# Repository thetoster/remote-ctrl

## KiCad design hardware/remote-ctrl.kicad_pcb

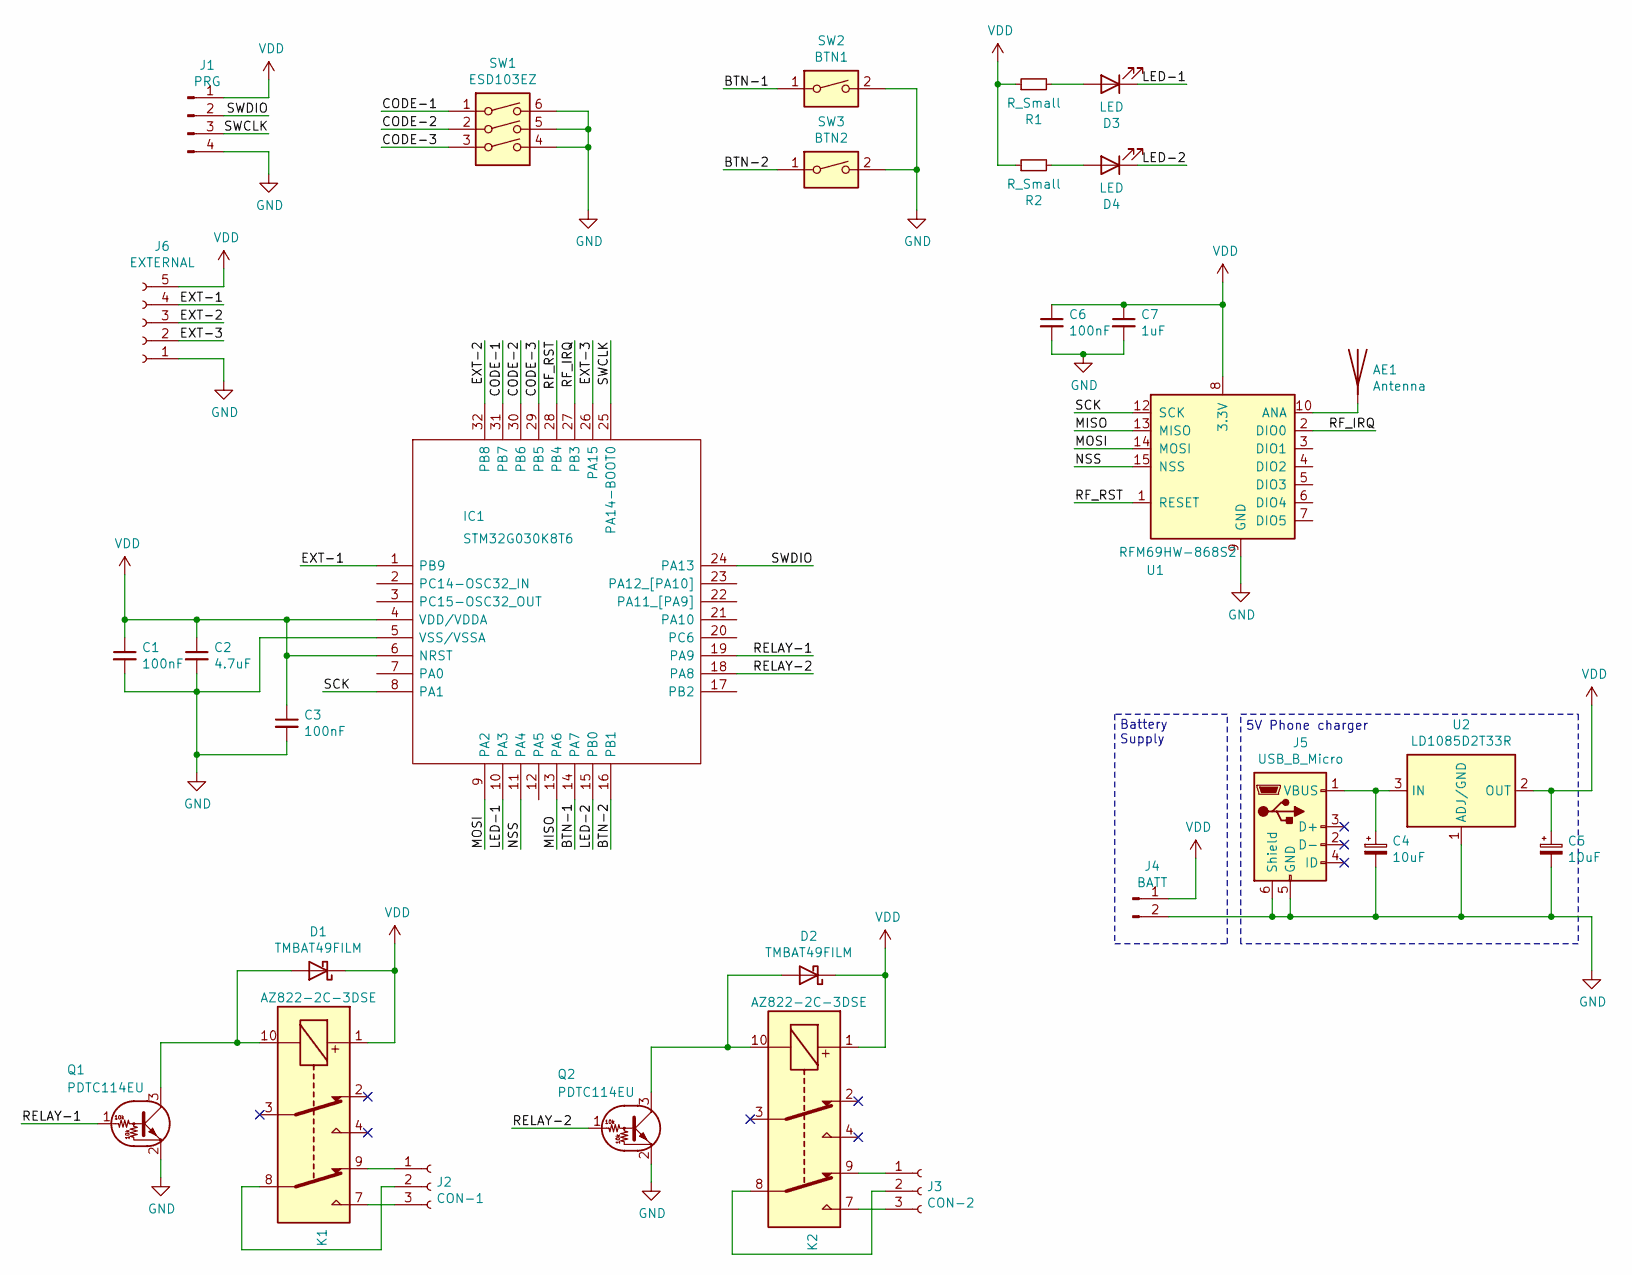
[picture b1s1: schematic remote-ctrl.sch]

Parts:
AE1: Antenna; TestPoint_Pad_2.0x2.0mm
C1, C3, C6: 100nF; C_0805_2012Metric_Pad1.15x1.40mm_HandSolder
C2: 4.7uF; C_0805_2012Metric_Pad1.15x1.40mm_HandSolder
C4, C5: 10uF; CP_Elec_4x5.3
C7: 1uF; C_0805_2012Metric_Pad1.15x1.40mm_HandSolder
D1, D2: TMBAT49FILM; D_MELF
D3, D4: LED; D_1206_3216Metric
IC1: STM32G030K8T6; QFP80P900X900X160-32N; Manufacturer_Part_Number STM32G030K8T6; Mouser Part Number 511-STM32G030K8T6
J1: PRG; PinHeader_1x04_P2.54mm_Vertical
J2: CON-1; TerminalBlock_bornier-3_P5.08mm
J3: CON-2; TerminalBlock_bornier-3_P5.08mm
J4: BATT; PinHeader_1x02_P2.54mm_Vertical
J5: USB_B_Micro; USB_Micro-B_Molex-105017-0001
J6: EXTERNAL; PinHeader_1x05_P2.54mm_Vertical
K1, K2: AZ822-2C-3DSE; Relay_DPDT_FRT5
Q1, Q2: PDTC114EU; SOT-323_SC-70_Handsoldering
R1, R2: R_Small; R_0805_2012Metric_Pad1.15x1.40mm_HandSolder
SW1: ESD103EZ; SW_DIP_SPSTx03_Slide_9.78x9.8mm_W8.61mm_P2.54mm
SW2: BTN1; SW_SPST_Omron_B3FS-101xP
SW3: BTN2; SW_SPST_Omron_B3FS-101xP
U1: RFM69HW-868S2; HOPERF_RFM69HW
U2: LD1085D2T33R; TO-263-3_TabPin2

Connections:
/BTN-1: IC1.14 (PA7), SW2.1
/BTN-2: IC1.16 (PB1), SW3.1
/CODE-1: IC1.31 (PB7), SW1.1
/CODE-2: IC1.30 (PB6), SW1.2
/CODE-3: IC1.29 (PB5), SW1.3
/EXT-1: IC1.1 (PB9), J6.4
/EXT-2: IC1.32 (PB8), J6.3
/EXT-3: IC1.26 (PA15), J6.2
/LED-1: D3.1 (K), IC1.10 (PA3)
/LED-2: D4.1 (K), IC1.15 (PB0)
/MISO: IC1.13 (PA6), U1.13 (MISO)
/MOSI: IC1.9 (PA2), U1.14 (MOSI)
/NSS: IC1.11 (PA4), U1.15 (NSS)
/RELAY-1: IC1.19 (PA9), Q1.1 (B)
/RELAY-2: IC1.18 (PA8), Q2.1 (B)
/RF_IRQ: IC1.27 (PB3), U1.2 (DIO0)
/RF_RST: IC1.28 (PB4), U1.1 (RESET)
/SCK: IC1.8 (PA1), U1.12 (SCK)
/SWCLK: IC1.25 (PA14-BOOT0), J1.3
/SWDIO: IC1.24 (PA13), J1.2
GND: C1.2, C2.2, C3.2, C4.2, C5.2, C6.2, C7.2, IC1.5 (VSS/VSSA), J1.4, J4.2, J5.5 (GND), J5.6 (Shield), J6.1, Q1.2 (E), Q2.2 (E), SW1.4, SW1.5, SW1.6, SW2.2, SW3.2, U1.9 (GND), U1.11 (GND), U2.1 (ADJ/GND)
unnamed: AE1.1, U1.10 (ANA)
unnamed: C4.1, J5.1 (VBUS), U2.3 (IN)
unnamed: D1.2 (A), K1.10, Q1.3 (C)
unnamed: D2.2 (A), K2.10, Q2.3 (C)
unnamed: D3.2 (A), R1.2
unnamed: D4.2 (A), R2.2
unnamed: J2.1, K1.9
unnamed: J2.2, K1.8
unnamed: J2.3, K1.7
unnamed: J3.1, K2.9
unnamed: J3.2, K2.8
unnamed: J3.3, K2.7
VDD: C1.1, C2.1, C3.1, C5.1, C6.1, C7.1, D1.1 (K), D2.1 (K), IC1.4 (VDD/VDDA), IC1.6 (NRST), J1.1, J4.1, J6.5, K1.1, K2.1, R1.1, R2.1, U1.8 (3.3V), U2.2 (OUT)

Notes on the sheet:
Battery Supply
5V Phone charger

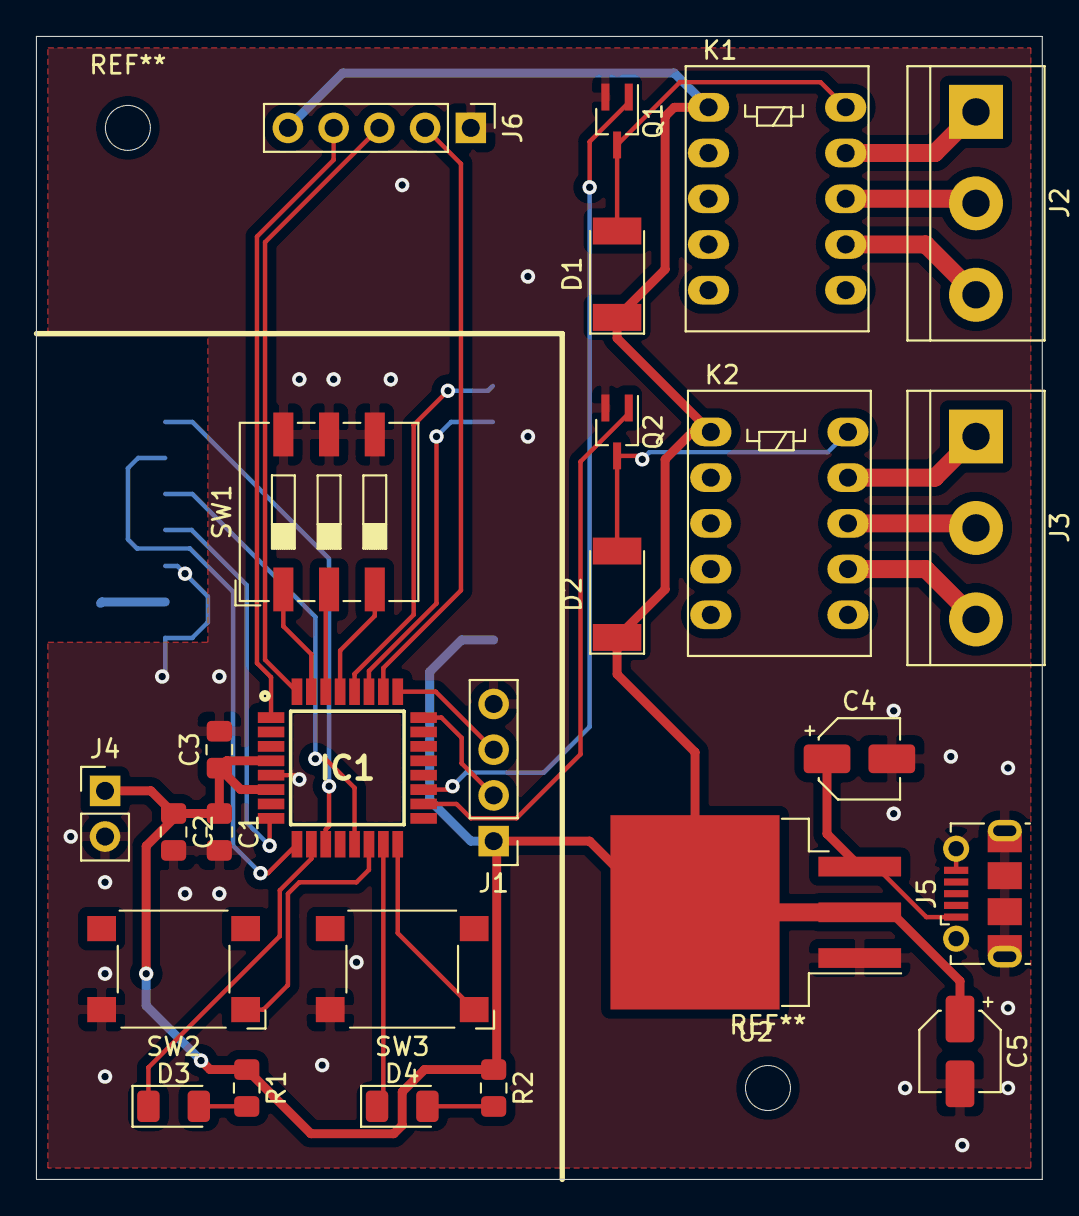
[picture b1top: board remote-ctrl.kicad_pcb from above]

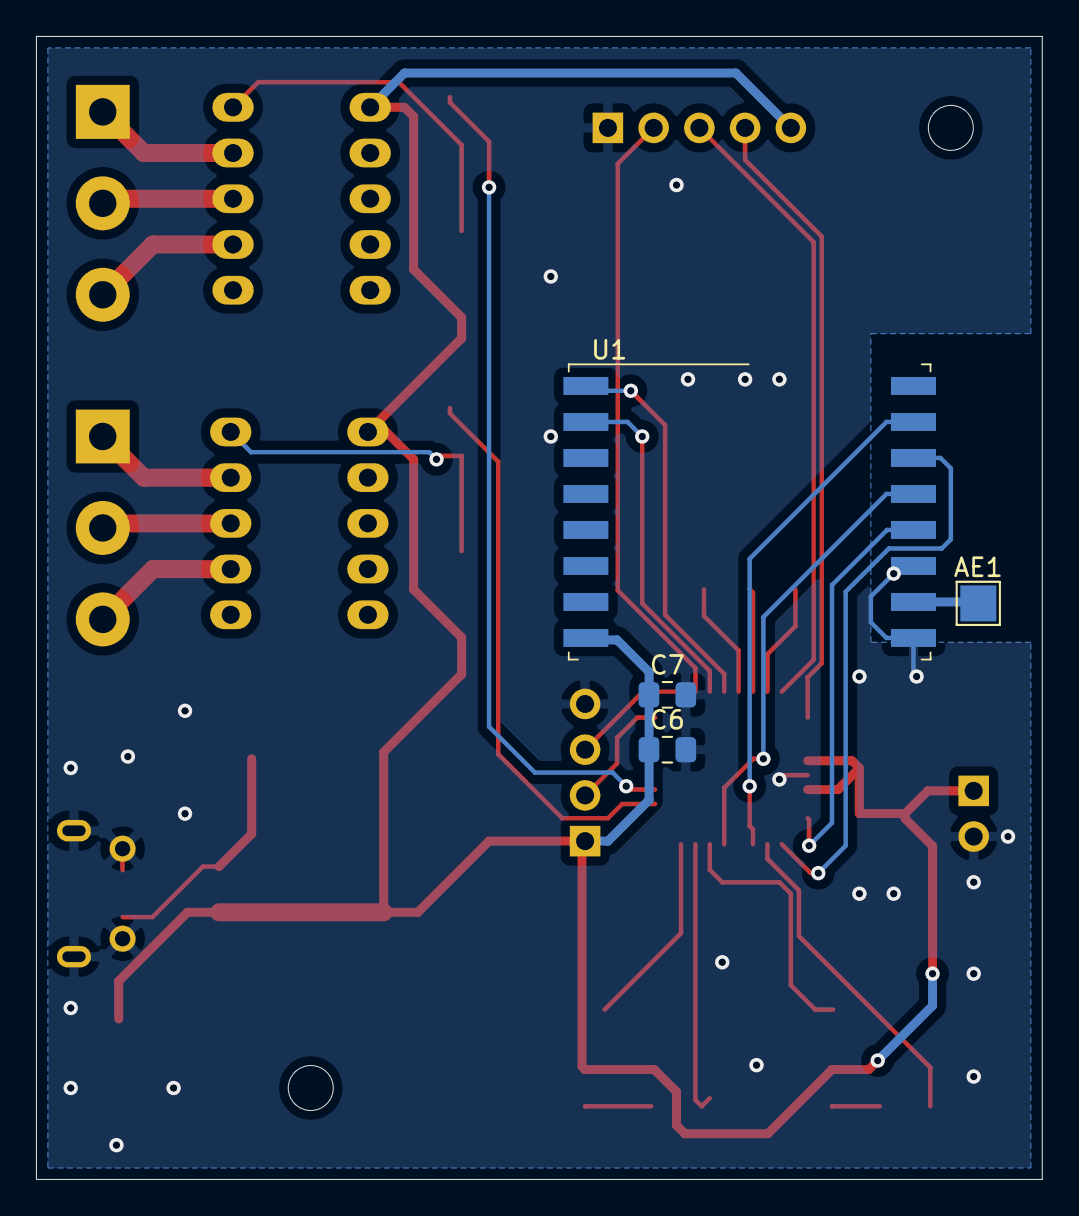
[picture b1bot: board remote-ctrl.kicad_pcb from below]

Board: 2 copper layers, 55.9 x 63.5 mm, 30 parts (4 on the bottom side), 34 nets.

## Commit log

2020-10-11 Initial commit of hardware
2020-10-12 removed 230VC section, added footprint and components from TME
2020-10-12 Added external port, some pin remaped, initial PCB
2020-10-14 Selected elements for BOM
